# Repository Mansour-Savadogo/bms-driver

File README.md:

# param-driver

This is an example use of libcsp and libparam to send commands to a remote device.

Before commands can be sent, you must initialize the serial port you are using. The way this is done depends on your hardware. I will add a sample initialization for a Raspberry Pi later.

# Requirements

libcsp/libparam library

sudo apt install git build-essential libsocketcan-dev can-utils libzmq3-dev pkg-config fonts-powerline python3-pip libelf-dev
sudo pip3 install meson ninja

# Installing
meson setup builddir
meson compile -C builddir

By default the application is not installed on your device. An executable is compiled and can be run using ./builddir/can_test.

# Printing the board
Full CAM files are contained in CAM_Files. The Gerber files can be read by most ECAD software or sent directly to a fab to be printed.

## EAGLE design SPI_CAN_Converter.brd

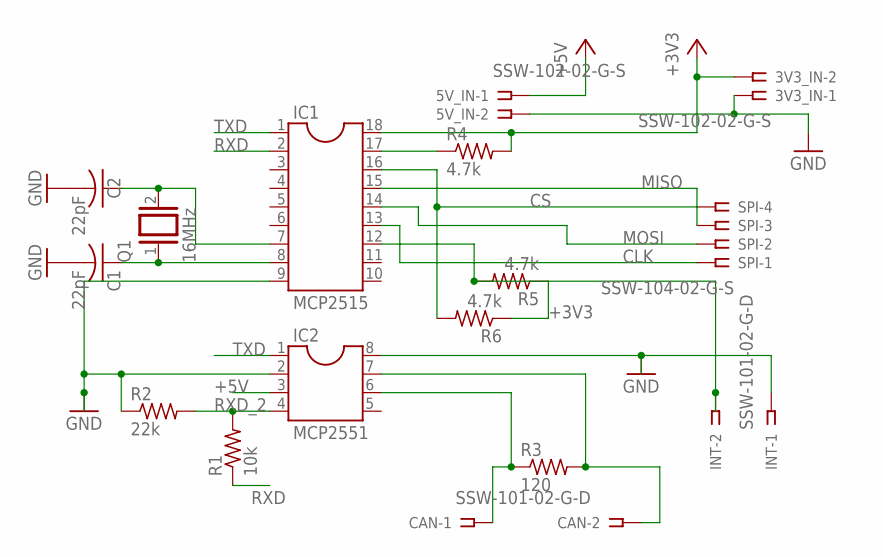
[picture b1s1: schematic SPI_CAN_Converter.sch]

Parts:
3V3_IN, 5V_IN: SSW-102-02-G-S
C1, C2: 22pF; C050-024X044
CAN: SSW-101-02-G-D
IC1: MCP2515; DIL18
IC2: MCP2551; DIL08
INT: SSW-101-02-G-D
Q1: 16MHz; QS
R1: 10k; 0207/7
R2: 22k; 0207/7
R3: 120; 0207/7
R4, R5, R6: 4.7k; 0207/7
SPI: SSW-104-02-G-S

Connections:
+3V3: 3V3_IN.2, IC1.18, R4.2, R5.1, R6.1
+5V: 5V_IN.1, IC2.3
CLK: IC1.13, SPI.1
CS: IC1.16, R6.2, SPI.4
GND: 3V3_IN.1, 5V_IN.2, C1.2, C2.2, IC1.9, IC2.2, IC2.8, INT.1, R2.1
INT: IC1.12, INT.2, R5.2
MISO: IC1.15, SPI.3
MOSI: IC1.14, SPI.2
unnamed: CAN.2, IC2.7, R3.2
unnamed: CAN.1, IC2.6, R3.1
unnamed: C1.1, IC1.8, Q1.1
unnamed: C2.1, IC1.7, Q1.2
unnamed: IC1.17, R4.1
RXD: IC1.2, R1.1
RXD_2: IC2.4, R1.2, R2.2
TXD: IC1.1, IC2.1

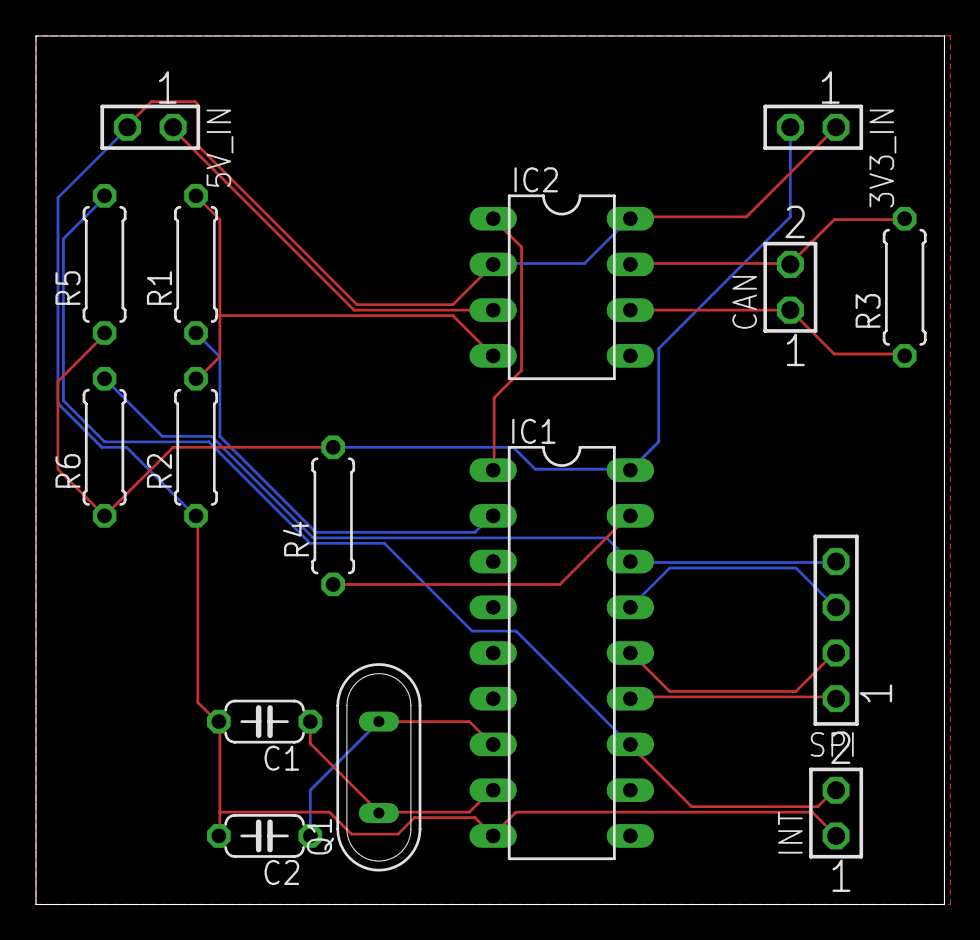
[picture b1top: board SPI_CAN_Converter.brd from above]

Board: 2 copper layers, 50.5 x 48.2 mm, 16 parts (0 on the bottom side), 16 nets.

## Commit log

2023-05-07 Set up connection starts. Not tested on hardware
2023-05-07 Added a header file to initConn
2023-05-07 Create README.md
    Added a README
2023-05-08 Added test PCB design files
    Simple PCB for a CAN-SPI converter. Designed in Autodesk Eagle, can be opened with Autodesk Fusion 360. Can be used to generate Gerber files.
2023-05-08 Added a definiton of __start_vmemand __stop_vmem because I had linker issues
2023-05-08 Added ZMQ connection for debugging and some messages in case no device is connected.
2023-05-12 Added an executable hard-coding the parameter instead of downloading lists
2023-05-21 Added files to describe Space Inventor PCDU
2023-05-21 Added support for some Space Inventor PCDU parameters
2023-05-21 Added test script
2023-06-05 Double checked variable types
2023-11-08 Replaced board files with Gerber files.
2023-11-08 cleaned up header file
2023-11-08 Changed README file
